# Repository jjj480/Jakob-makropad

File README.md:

# Jakob-makropad
a makropad for daily use

Parts:
2 EC11 encoders
4 Blank DSA keycaps
M3x16mm screws
M3x5mmx4mm heatset inserts
3 SK6812 MINI-E LEDs
3D printed case 
PCB
Seeed XIAO RP2040
4 MX-Style switches

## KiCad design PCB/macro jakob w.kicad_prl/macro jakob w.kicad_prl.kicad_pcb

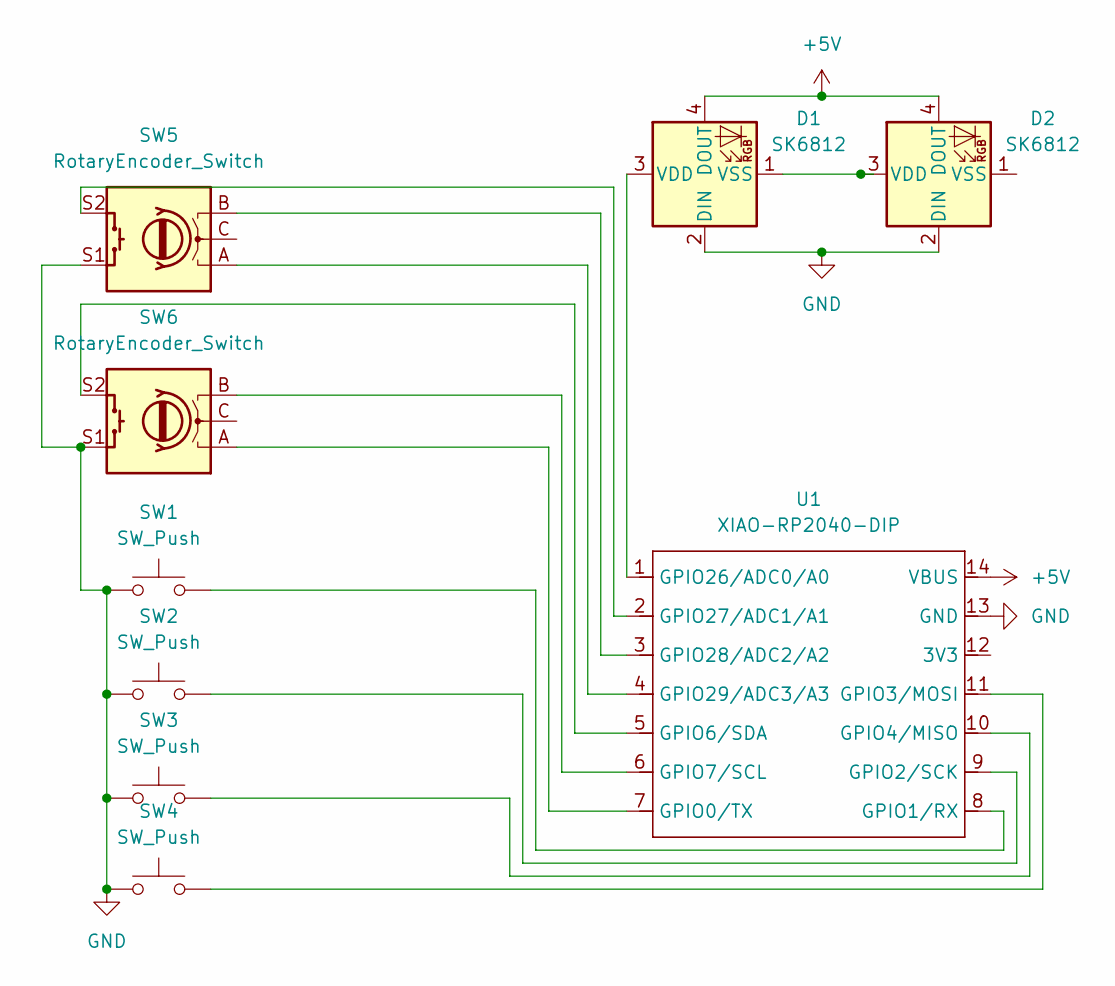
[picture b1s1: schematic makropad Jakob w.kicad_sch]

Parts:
D1, D2: SK6812; LED_SK6812_PLCC4_5.0x5.0mm_P3.2mm
SW1, SW2, SW3, SW4: SW_Push; SW_Cherry_MX_1.00u_PCB
SW5, SW6: RotaryEncoder_Switch; RotaryEncoder_Alps_EC11E-Switch_Vertical_H20mm_CircularMoun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
U1: XIAO-RP2040-DIP; XIAO-RP2040-SMD

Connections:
+5V: D1.4 (DOUT), D2.4 (DOUT), U1.14 (VBUS)
GND: D1.2 (DIN), D2.2 (DIN), SW1.1, SW2.1, SW3.1, SW4.1, SW5.S1, SW6.S1, U1.13 (GND)
unnamed: D1.3 (VDD), U1.1 (GPIO26/ADC0/A0)
unnamed: D1.1 (VSS), D2.3 (VDD)
unnamed: SW6.A, U1.7 (GPIO0/TX)
unnamed: SW1.2, U1.8 (GPIO1/RX)
unnamed: SW2.2, U1.9 (GPIO2/SCK)
unnamed: SW4.2, U1.11 (GPIO3/MOSI)
unnamed: SW3.2, U1.10 (GPIO4/MISO)
unnamed: SW6.S2, U1.5 (GPIO6/SDA)
unnamed: SW6.B, U1.6 (GPIO7/SCL)
unnamed: SW5.S2, U1.2 (GPIO27/ADC1/A1)
unnamed: SW5.B, U1.3 (GPIO28/ADC2/A2)
unnamed: SW5.A, U1.4 (GPIO29/ADC3/A3)

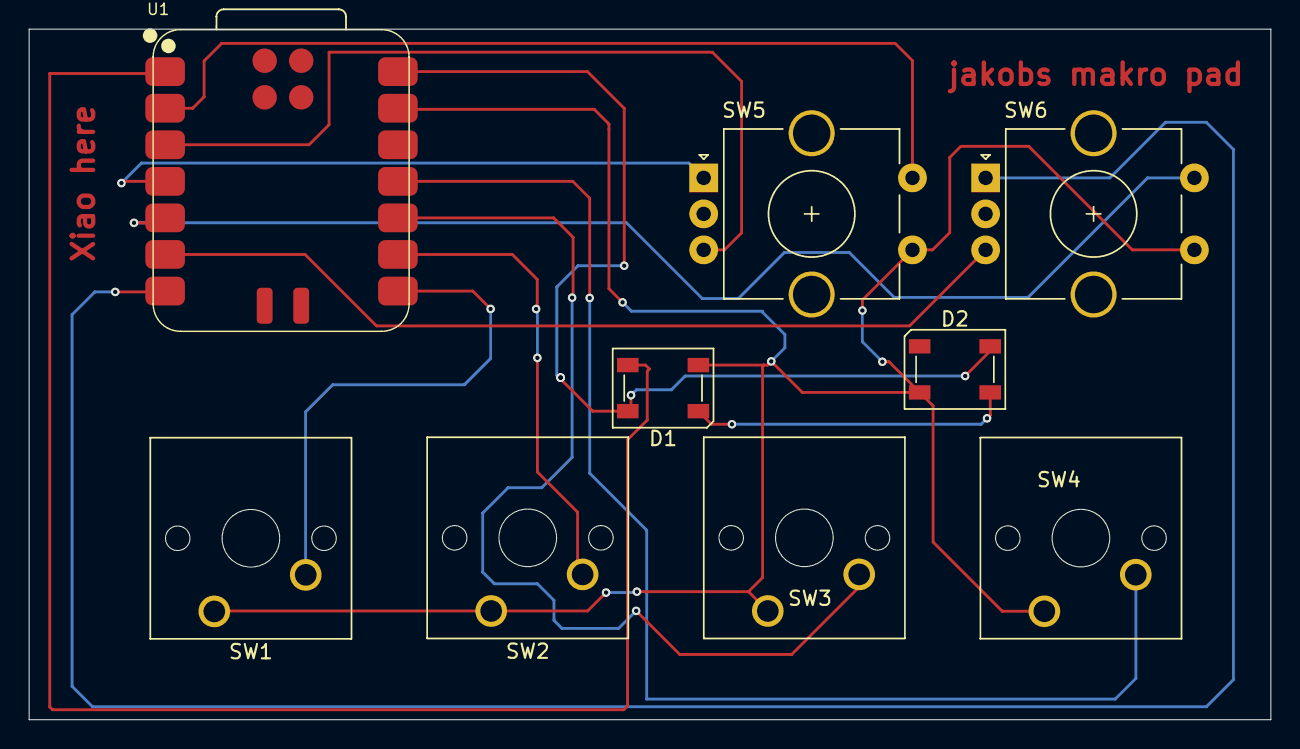
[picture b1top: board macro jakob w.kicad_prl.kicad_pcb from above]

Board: 2 copper layers, 86.2 x 48.0 mm, 9 parts (0 on the bottom side), 14 nets.
